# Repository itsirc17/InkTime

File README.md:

# InkTime

Designed for optimal energy efficiency, InkTime is a custom e-paper smartwatch project. This document serves as a complete technical reference for the project.

## Block Diagram(Architecture)

```mermaid
graph TD
    %% Central MCU
    MCU[nRF52840 Microcontroller]

    %% Power Subsystem
    USB[USB-C Port] -->|5V VBUS| ESD[ESD Protection USBLC6]
    ESD -->|5V| CHG[BQ25180 LiPo Charger]
    DCDC -->|3.3V System Power| MCU
    DCDC -->|3.3V| SENSORS
    BATT[LiPo Battery] <--> CHG
    BATT <--> FG[MAX17048 Fuel Gauge]
    BATT -->|V_BAT| DCDC[RT6160 Buck-Boost DC/DC]

    %% Interconnects
    MCU <-->|I2C Bus| IMU[BMA421 Accelerometer]
    MCU <-->|I2C Bus| HAP[DRV2605 Haptic Driver]
    MCU <-->|I2C Bus| CHG
    MCU <-->|I2C Bus| FG

    MCU -->|SPI & Control| EPD[E-Paper Display Connector]
    MCU -->|PWM/Trigger| HAP
    HAP -->|Analog| LRA[Haptic Motor]

    %% Inputs
    BTN1[SW_UP] -->|GPIO| MCU
    BTN2[SW_ENT] -->|GPIO| MCU
    BTN3[SW_DN] -->|GPIO| MCU

    %% SWD
    SWD[TC2030-IDC SWD Port] <-->|Programming/Debug| MCU
```

## Functionality

### Power Subsystem & Energy Management

Charging Input: Power is supplied via a 16-pin USB-C connector. The data lines are safeguarded against plug-in transients by a USBLC6-2SC6Y TVS diode array.

Battery Charging (BQ25180): A highly integrated linear charger tailored for small wearables. It features power-path management (allowing the device to run on USB power while charging) and interfaces with the MCU via I2C for dynamic charge current configuration and fault monitoring.

Fuel Gauge (MAX17048): Connected directly to the battery, this IC determines the State-Of-Charge (SOC) using voltage measurements and characterization algorithms. This eliminates the need for a power-wasting current sense resistor, reporting battery percentages cleanly over I2C.

Voltage Regulation (RT6160): Because LiPo voltages fluctuate between 4.2V and 3.0V, this Buck-Boost converter guarantees a stable 3.3V supply. It bucks down when the battery is full and boosts up as it depletes, maximizing the usable battery cycle.

Power Consumption Targets: The system aims for < 10 µA in Deep Sleep (MCU + Sensors suspended + Power ICs quiescent). Active processing consumes roughly 4-6 mA, while a display update will draw 10-15 mA for 2-3 seconds depending on the panel.

### Motion Sensing

IMU (BMA421): A Bosch ultra-low-power accelerometer optimized for wearables. It features a built-in hardware step-counter, allowing the MCU to remain in deep sleep while the sensor actively counts steps. The MCU only wakes periodically to sync the data via I2C.

### User Interface & Output

E-Paper Display (EPD): Interfaces through a standard 24-pin FPC connector. The onboard charge-pump circuit utilizes MBR0530 diodes, inductors, and DMG2305UX switching MOSFETs to generate the high drive voltages (+15V/-15V) needed to manipulate the e-ink microcapsules. The MCU can completely sever power to this circuit to prevent standby leakage.

Haptic Feedback (DRV2605): An I2C-connected haptic driver that contains an internal library of waveforms (clicks, buzzes, ramps). This delivers crisp tactile feedback to ERM or LRA motors without requiring the MCU to generate complex PWM signals.

Physical Inputs: Three tactile buttons (SW_UP, SW_ENT, SW_DN) feature hardware debouncing via 0.1uF capacitors. They utilize internal pull-ups and trigger MCU interrupts to wake the system from sleep.

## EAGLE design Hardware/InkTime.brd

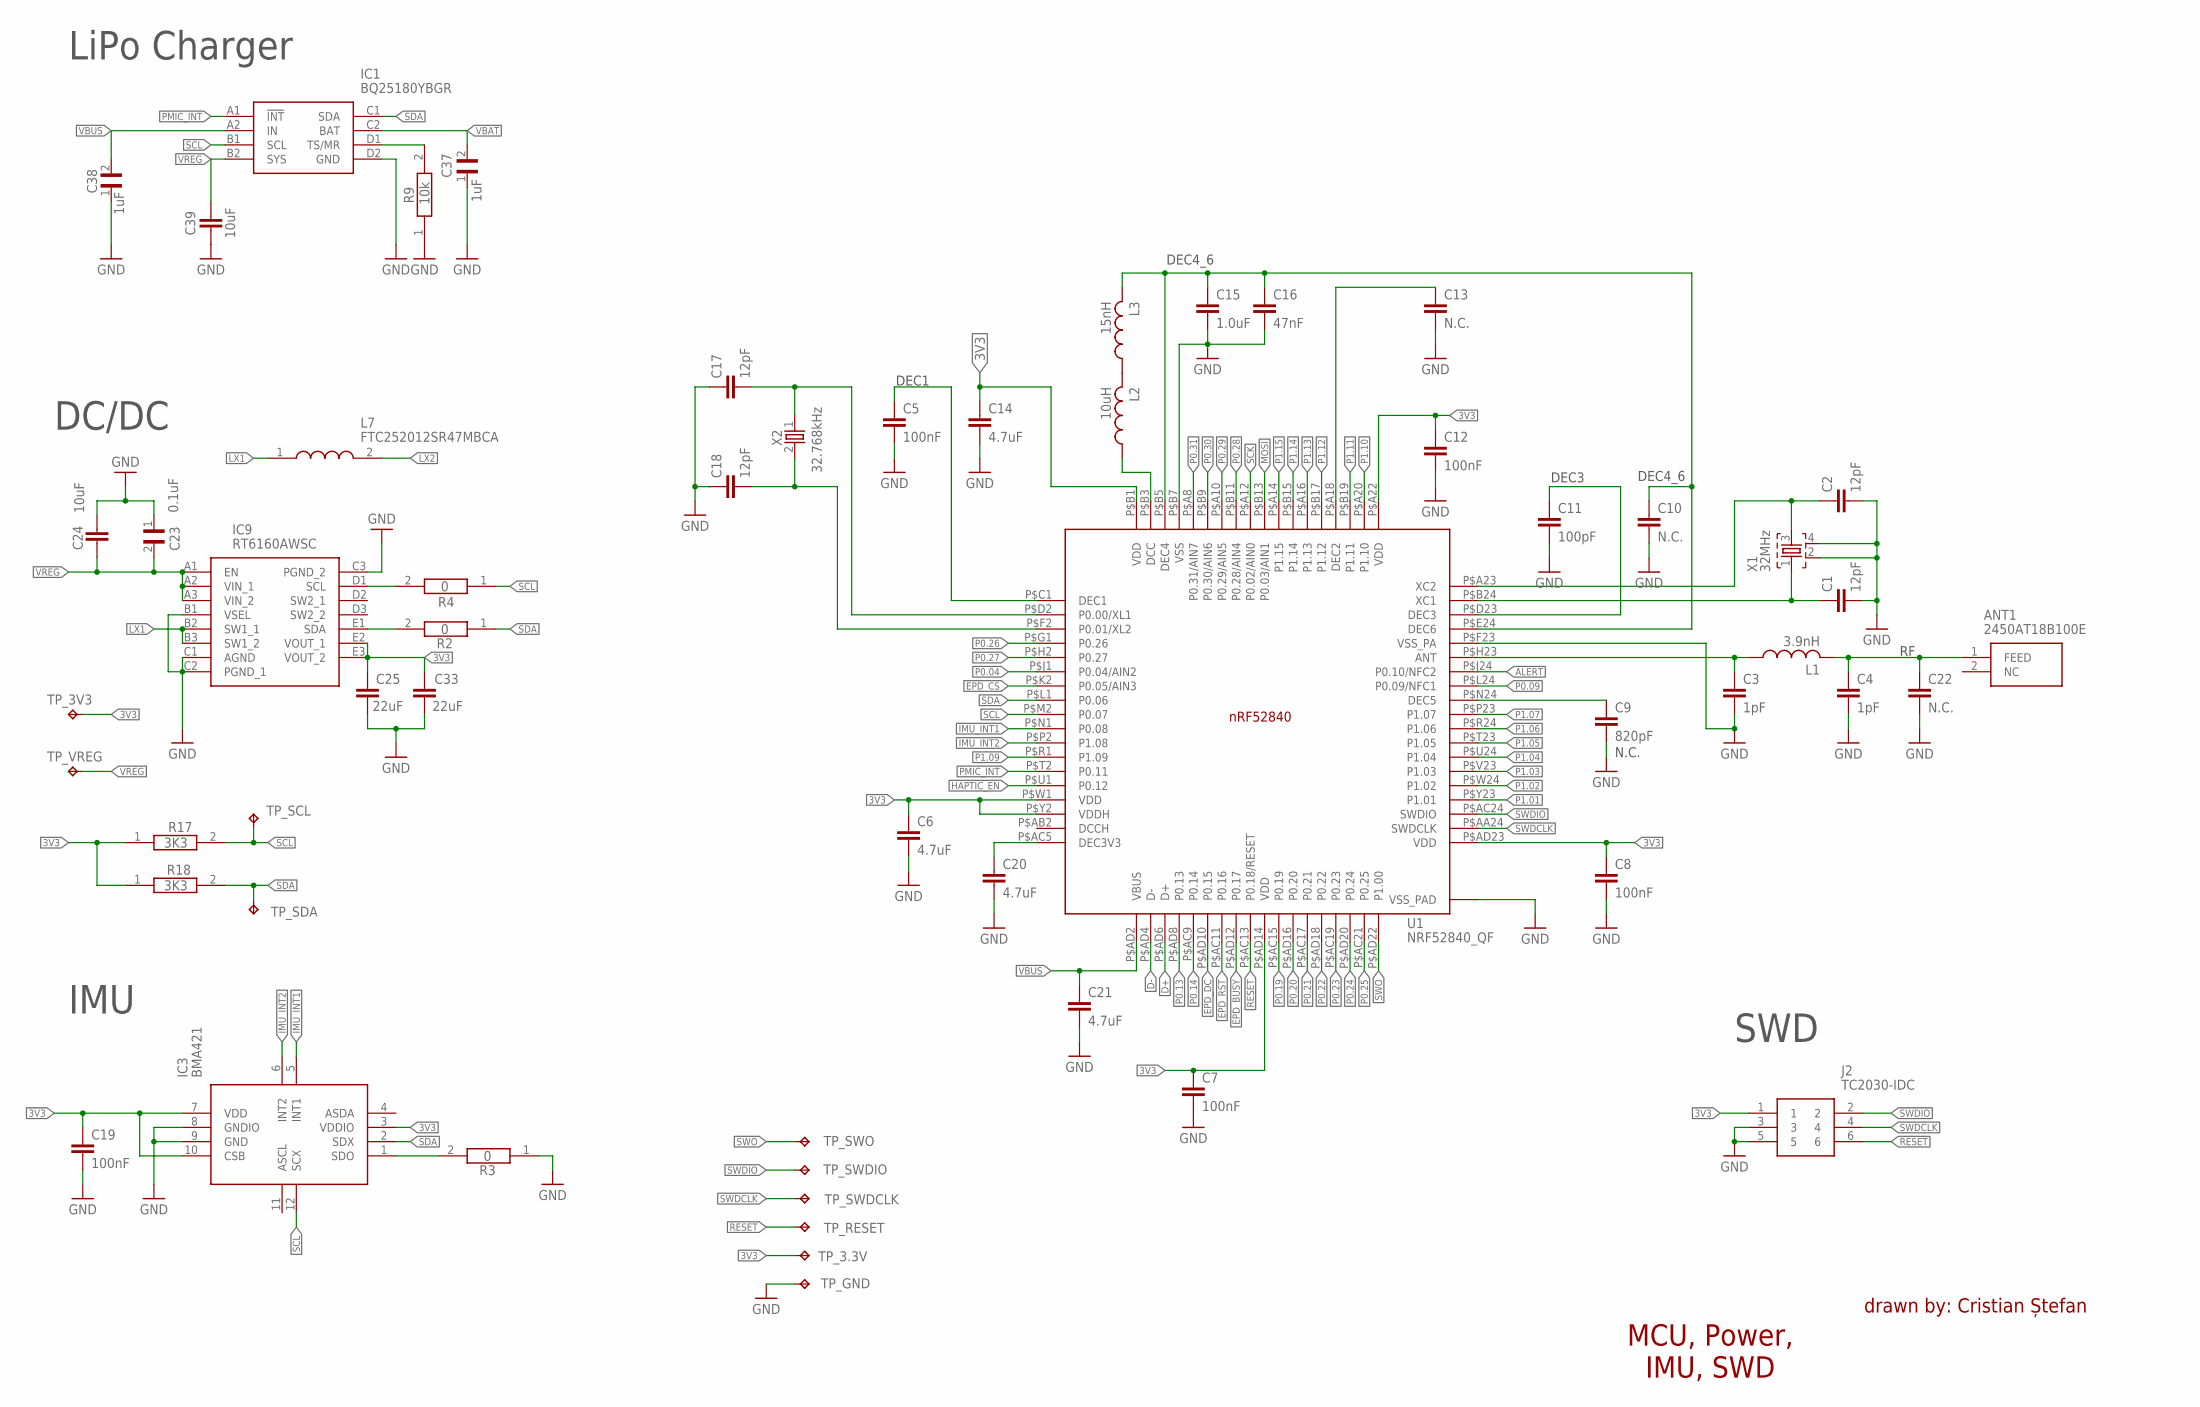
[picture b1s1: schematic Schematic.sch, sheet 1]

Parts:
ANT1: 2450AT18B100E; 2450AT18B100E_ANTC3216X140N
C1, C2, C17, C18: 12pF; NORDIC_NRF_3_RESC0201_L
C3, C4: 1pF; NORDIC_NRF_3_RESC0201_L
C5, C7, C8, C12, C19: 100nF; NORDIC_NRF_3_RESC0201_L
C6, C14, C20, C21: 4.7uF; NORDIC_NRF_3_RESC0402_L
C9: 820pF; NORDIC_NRF_3_RESC0201_L
C10, C13, C22: N.C.; NORDIC_NRF_3_RESC0201_L
C11: 100pF; NORDIC_NRF_3_RESC0201_L
C15: 1.0uF; NORDIC_NRF_3_RESC0402_L
C16: 47nF; NORDIC_NRF_3_RESC0201_L
C23: 0.1uF; GRM011R60J152KE01L_2_CAPC0201X13N
C24, C39: 10uF; NORDIC_NRF_3_RESC0402_L
C25, C33: 22uF; NORDIC_NRF_3_RESC0402_L
C37, C38: 1uF; GRM011R60J152KE01L_2_CAPC0201X13N
IC1: BQ25180YBGR; BQ25180YBGR_BGA8C40P2X4_100X155X50
IC3: BMA421; BMA423_BMA423
IC9: RT6160AWSC; RT6160AWSC_BGA15C40P3X5_140X230X60
J2: TC2030-IDC; TC2030-IDC_TC2030IDC
L1: 3.9nH; NORDIC_NRF_2_RESC0402_L
L2: 10uH; NORDIC_NRF_2_RESC0201_L
L3: 15nH; NORDIC_NRF_2_RESC0201_L
L7: FTC252012SR47MBCA; MLP2016SR47MT0S1_INDC2016X100N
R2, R3, R4: 0; CPF0201D7K68C1_0201
R9: 10k; CPF0201D7K68C1_0201
R17, R18: 3K3; CPF0201D7K68C1_0201
TP_3.3V, TP_3V3: HECTOR_WATCH_1_TPTP20R; HECTOR_WATCH_1_TP20R
TP_GND: HECTOR_WATCH_1_TPTP20R; HECTOR_WATCH_1_TP20R
TP_RESET: HECTOR_WATCH_1_TPTP20R; HECTOR_WATCH_1_TP20R
TP_SCL: HECTOR_WATCH_1_TPTP20R; HECTOR_WATCH_1_TP20R
TP_SDA: HECTOR_WATCH_1_TPTP20R; HECTOR_WATCH_1_TP20R
TP_SWDCLK: HECTOR_WATCH_1_TPTP20R; HECTOR_WATCH_1_TP20R
TP_SWDIO: HECTOR_WATCH_1_TPTP20R; HECTOR_WATCH_1_TP20R
TP_SWO: HECTOR_WATCH_1_TPTP20R; HECTOR_WATCH_1_TP20R
TP_VREG: HECTOR_WATCH_1_TPTP20R; HECTOR_WATCH_1_TP20R
U1: NRF52840_QF; NORDIC_NRF_4_AQFN50P700X700X85_HS-74N
X1: 32MHz; NORDIC_NRF_BT-XTAL_2016_N
X2: 32.768kHz; NORDIC_NRF_1_XTAL_3215_N

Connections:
3V3: C6.1, C7.1, C8.1, C12.1, C14.1, C19.1, C25.2, C33.2, IC3.3 (VDDIO), IC3.7 (VDD), IC3.10 (CSB), IC9.E2 (VOUT_1), IC9.E3 (VOUT_2), J2.1, R17.1, R18.1, TP_3.3V.TP, TP_3V3.TP, U1.P$A22 (VDD), U1.P$AD14 (VDD), U1.P$AD23 (VDD), U1.P$B1 (VDD), U1.P$W1 (VDD), U1.P$Y2 (VDDH); also elsewhere on the board
ALERT: U1.P$J24 (P0.10/NFC2); also elsewhere on the board
CACA: C5.1, U1.P$C1 (DEC1)
CACA2: C13.1, U1.P$A18 (DEC2)
D+: U1.P$AD6 (D+); also elsewhere on the board
D-: U1.P$AD4 (D-); also elsewhere on the board
EPD_BUSY: U1.P$AD12 (P0.17); also elsewhere on the board
EPD_CS: U1.P$K2 (P0.05/AIN3); also elsewhere on the board
EPD_DC: U1.P$AD10 (P0.15); also elsewhere on the board
EPD_RST: U1.P$AC11 (P0.16); also elsewhere on the board
GND: C1.2, C2.2, C3.2, C4.2, C5.2, C6.2, C7.2, C8.2, C9.2, C10.2, C11.2, C12.2, C13.2, C14.2, C15.2, C16.2, C17.1, C18.1, C19.2, C20.2, C21.2, C22.2, C23.1, C24.1, C25.1, C33.1, C37.1, C38.1, C39.2, IC1.D2 (GND), IC3.8 (GNDIO), IC3.9 (GND), IC9.B1 (VSEL), IC9.C1 (AGND), IC9.C2 (PGND_1), IC9.C3 (PGND_2), J2.3, J2.5, R3.1, R9.1, TP_GND.TP, U1.P$74 (VSS_PAD), U1.P$75 (VSS_PAD), U1.P$76 (VSS_PAD), U1.P$77 (VSS_PAD), U1.P$78 (VSS_PAD), U1.P$79 (VSS_PAD), U1.P$80 (VSS_PAD), U1.P$81 (VSS_PAD), U1.P$82 (VSS_PAD), U1.P$83 (VSS_PAD), U1.P$84 (VSS_PAD), U1.P$85 (VSS_PAD), U1.P$86 (VSS_PAD), U1.P$87 (VSS_PAD), U1.P$88 (VSS_PAD), U1.P$89 (VSS_PAD), U1.P$90 (VSS_PAD), U1.P$B7 (VSS), U1.P$F23 (VSS_PA), X1.2, X1.4; also elsewhere on the board
HAPTIC_EN: U1.P$U1 (P0.12); also elsewhere on the board
IMU_INT1: IC3.5 (INT1), U1.P$N1 (P0.08)
IMU_INT2: IC3.6 (INT2), U1.P$P2 (P1.08)
LX1: IC9.B2 (SW1_1), IC9.B3 (SW1_2), L7.1
LX2: L7.2
MOSI: U1.P$B13 (P0.03/AIN1); also elsewhere on the board
unnamed: IC9.E1 (SDA), R2.2
unnamed: IC9.D1 (SCL), R4.2
unnamed: IC3.1 (SDO), R3.2
unnamed: C20.1, U1.P$AC5 (DEC3V3)
unnamed: C9.1, U1.P$N24 (DEC5)
unnamed: C3.1, L1.1, U1.P$H23 (ANT)
unnamed: C2.1, U1.P$A23 (XC2), X1.3
unnamed: ANT1.1 (FEED), C4.1, C22.1, L1.2
unnamed: C11.1, U1.P$D23 (DEC3)
unnamed: IC1.D1 (TS/MR), R9.2
unnamed: L2.2, L3.1
unnamed: C1.1, U1.P$B24 (XC1), X1.1
unnamed: C17.2, U1.P$D2 (P0.00/XL1), X2.1
unnamed: L2.1, U1.P$B3 (DCC)
unnamed: C10.1, C15.1, C16.1, L3.2, U1.P$B5 (DEC4), U1.P$E24 (DEC6)
unnamed: C18.2, U1.P$F2 (P0.01/XL2), X2.2
P0.04: U1.P$J1 (P0.04/AIN2)
P0.09: U1.P$L24 (P0.09/NFC1)
P0.13: U1.P$AD8 (P0.13); also elsewhere on the board
P0.14: U1.P$AC9 (P0.14); also elsewhere on the board
P0.19: U1.P$AC15 (P0.19)
P0.20: U1.P$AD16 (P0.20)
P0.21: U1.P$AC17 (P0.21)
P0.22: U1.P$AD18 (P0.22)
P0.23: U1.P$AC19 (P0.23)
P0.24: U1.P$AD20 (P0.24)
P0.25: U1.P$AC21 (P0.25)
P0.26: U1.P$G1 (P0.26)
P0.27: U1.P$H2 (P0.27)
P0.28: U1.P$B11 (P0.28/AIN4)
P0.29: U1.P$A10 (P0.29/AIN5)
P0.30: U1.P$B9 (P0.30/AIN6)
P0.31: U1.P$A8 (P0.31/AIN7)
P1.01: U1.P$Y23 (P1.01); also elsewhere on the board
P1.02: U1.P$W24 (P1.02); also elsewhere on the board
P1.03: U1.P$V23 (P1.03)
P1.04: U1.P$U24 (P1.04)
P1.05: U1.P$T23 (P1.05)
P1.06: U1.P$R24 (P1.06)
P1.07: U1.P$P23 (P1.07)
P1.09: U1.P$R1 (P1.09)
P1.10: U1.P$A20 (P1.10)
P1.11: U1.P$B19 (P1.11)
P1.12: U1.P$B17 (P1.12)
P1.13: U1.P$A16 (P1.13)
P1.14: U1.P$B15 (P1.14)
P1.15: U1.P$A14 (P1.15)
PMIC_INT: IC1.A1 (!INT), U1.P$T2 (P0.11)
RESET: J2.6, TP_RESET.TP, U1.P$AC13 (P0.18/RESET)
SCK: U1.P$A12 (P0.02/AIN0); also elsewhere on the board
SCL: IC1.B1 (SCL), IC3.12 (SCX), R4.1, R17.2, TP_SCL.TP, U1.P$M2 (P0.07); also elsewhere on the board
SDA: IC1.C1 (SDA), IC3.2 (SDX), R2.1, R18.2, TP_SDA.TP, U1.P$L1 (P0.06); also elsewhere on the board
SWDCLK: J2.4, TP_SWDCLK.TP, U1.P$AA24 (SWDCLK)
SWDIO: J2.2, TP_SWDIO.TP, U1.P$AC24 (SWDIO)
SWO: TP_SWO.TP, U1.P$AD22 (P1.00)
VBAT: C37.2, IC1.C2 (BAT); also elsewhere on the board
VBUS: C21.1, C38.2, IC1.A2 (IN), U1.P$AD2 (VBUS); also elsewhere on the board
VREG: C23.2, C24.2, C39.1, IC1.B2 (SYS), IC9.A1 (EN), IC9.A2 (VIN_1), IC9.A3 (VIN_2), TP_VREG.TP

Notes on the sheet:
LiPo Charger
N.C.
DEC4_6
DEC3
DEC1
DC/DC
IMU
SWD
drawn by: Cristian Ștefan
MCU, Power, IMU, SWD

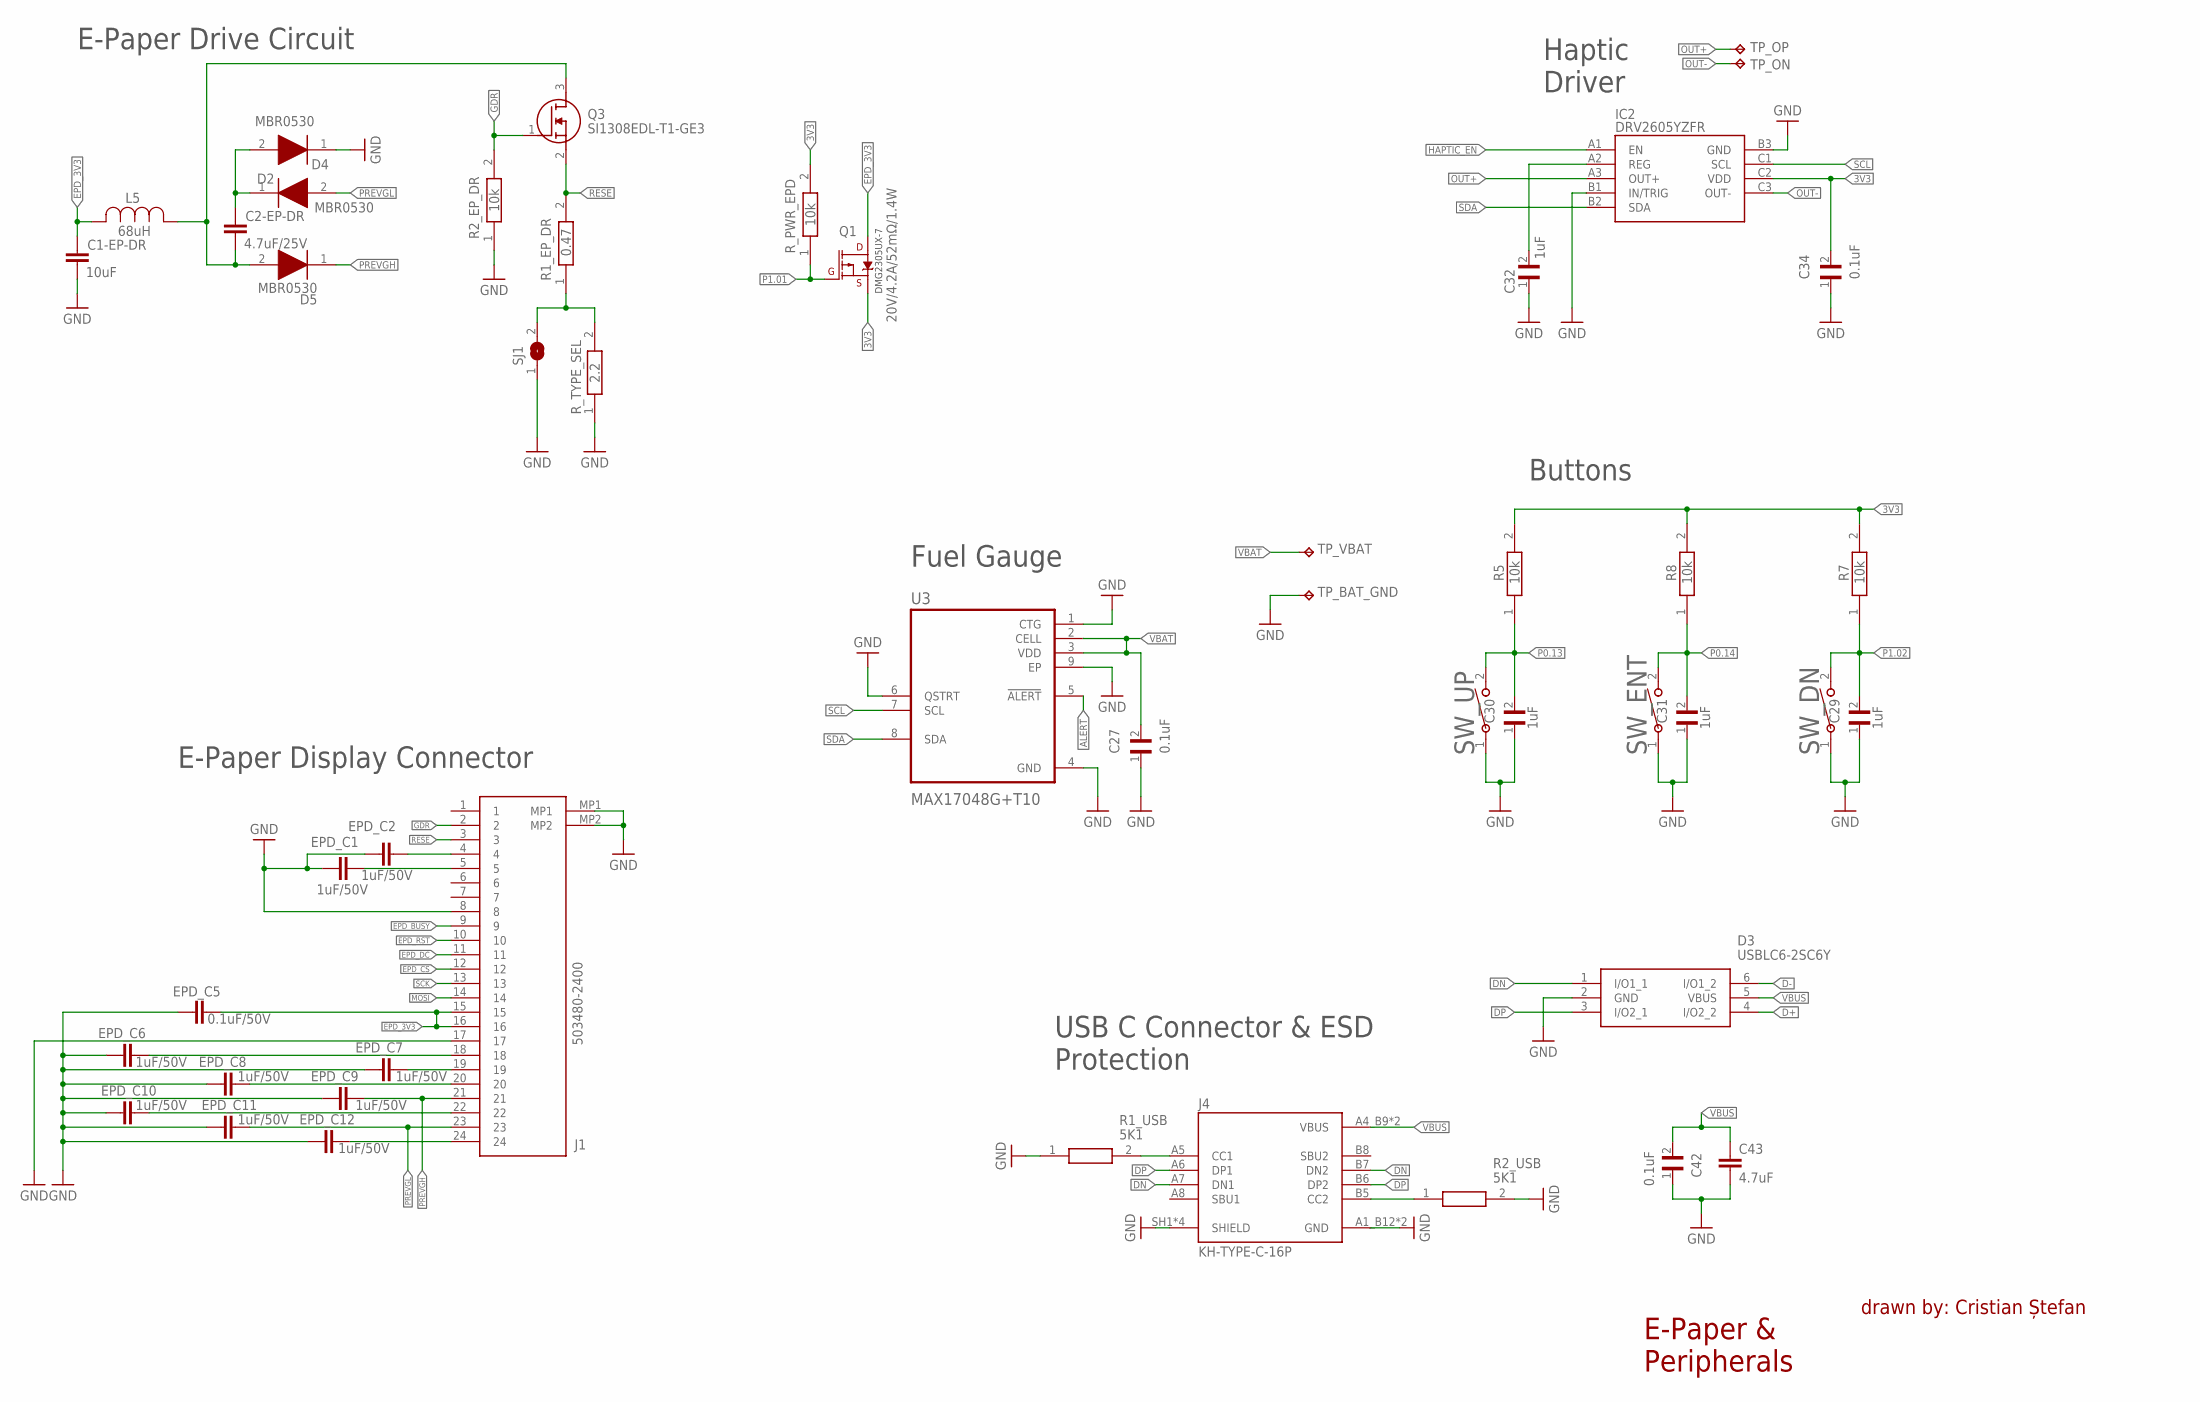
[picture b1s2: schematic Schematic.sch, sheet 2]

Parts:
C1-EP-DR: 10uF; NORDIC_NRF_3_RESC0402_L
C2-EP-DR: 4.7uF/25V; NORDIC_NRF_3_RESC0402_L
C27, C34, C42: 0.1uF; GRM011R60J152KE01L_2_CAPC0201X13N
C29, C30, C31, C32: 1uF; GRM011R60J152KE01L_2_CAPC0201X13N
C43: 4.7uF; NORDIC_NRF_3_RESC0402_L
D2, D4, D5: MBR0530; ESP32_C6_LIBRARY_5_SOD3716X135N
D3: USBLC6-2SC6Y; ESP32_C6_LIBRARY_3_SOT95P280X145-6N
EPD_C1, EPD_C2, EPD_C6, EPD_C7, EPD_C8, EPD_C9, EPD_C10, EPD_C11, EPD_C12: 1uF/50V; NORDIC_NRF_3_RESC0402_L
EPD_C5: 0.1uF/50V; NORDIC_NRF_3_RESC0402_L
IC2: DRV2605YZFR; DRV2605YZFR_BGA9C50P3X3_144X144X62
J1: 503480-2400; 503480-2400_5034802400
J4: KH-TYPE-C-16P; KH-TYPE-C-16P_KINGHELM_KH-TYPE-C-16P
L5: 68uH; ESP32_C6_LIBRARY_2_IND_4828-WE-TPC_WRE
Q1: 20V/4.2A/52mΩ/1.4W; ESP32_C6_LIBRARY_4_ESP32_C6_LIBRARY_4_ESP32_C6_LIBRARY_4_ES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
Q3: SI1308EDL-T1-GE3; ESP32_C6_LIBRARY_6_SOT65P210X110-3N
R1_EP_DR: 0.47; CPF0201D7K68C1_0201
R1_USB, R2_USB: 5K1; CPF0201D7K68C1_0201
R2_EP_DR, R5, R7, R8: 10k; CPF0201D7K68C1_0201
R_PWR_EPD: 10k; CPF0201D7K68C1_0201
R_TYPE_SEL: 2.2; CPF0201D7K68C1_0201
SJ1: ESP32_C6_LIBRARY_7_JUMPER_SJ
SW_DN: 2025-10-22_07-23-44_LIBRARY_EVP-AKE31A; 2025-10-22_07-23-44_LIBRARY_SW_EVP-AKE31A_PAN
SW_ENT: 2025-10-22_07-23-44_LIBRARY_EVP-AKE31A; 2025-10-22_07-23-44_LIBRARY_SW_EVP-AKE31A_PAN
SW_UP: 2025-10-22_07-23-44_LIBRARY_EVP-AKE31A; 2025-10-22_07-23-44_LIBRARY_SW_EVP-AKE31A_PAN
TP_BAT_GND: HECTOR_WATCH_1_TPTP20R; HECTOR_WATCH_1_TP20R
TP_ON: HECTOR_WATCH_1_TPTP20R; HECTOR_WATCH_1_TP20R
TP_OP: HECTOR_WATCH_1_TPTP20R; HECTOR_WATCH_1_TP20R
TP_VBAT: HECTOR_WATCH_1_TPTP20R; HECTOR_WATCH_1_TP20R
U3: MAX17048G+T10; ESP32_C6_LIBRARY_SON50P200X200X80-9N

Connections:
3V3: C34.2, IC2.C2 (VDD), Q1.2 (S), R5.2, R7.2, R8.2, R_PWR_EPD.2; also elsewhere on the board
ALERT: U3.5 (!ALERT); also elsewhere on the board
D+: D3.4 (I/O2_2); also elsewhere on the board
D-: D3.6 (I/O1_2); also elsewhere on the board
DN: D3.1 (I/O1_1), J4.A7 (DN1), J4.B7 (DN2)
DP: D3.3 (I/O2_1), J4.A6 (DP1), J4.B6 (DP2)
EPD_3V3: C1-EP-DR.1, EPD_C5.2, J1.15, J1.16, L5.2, Q1.3 (D)
EPD_BUSY: J1.9; also elsewhere on the board
EPD_CS: J1.12; also elsewhere on the board
EPD_DC: J1.11; also elsewhere on the board
EPD_RST: J1.10; also elsewhere on the board
GDR: J1.2, Q3.1 (G), R2_EP_DR.2
GND: C1-EP-DR.2, C27.1, C29.1, C30.1, C31.1, C32.1, C34.1, C42.1, C43.2, D3.2 (GND), D4.1 (K), EPD_C1.1, EPD_C2.1, EPD_C5.1, EPD_C6.1, EPD_C7.1, EPD_C8.1, EPD_C9.1, EPD_C10.1, EPD_C11.1, EPD_C12.1, IC2.B1 (IN/TRIG), IC2.B3 (GND), J1.8, J1.17, J1.MP1, J1.MP2, J4.A1_B12 (GND), J4.A12_B1 (GND), J4.SH1 (SHIELD), J4.SH2 (SHIELD), J4.SH3 (SHIELD), J4.SH4 (SHIELD), R1_USB.1, R2_EP_DR.1, R2_USB.2, R_TYPE_SEL.1, SJ1.1, SW_DN.1, SW_ENT.1, SW_UP.1, TP_BAT_GND.TP, U3.1 (CTG), U3.4 (GND), U3.6 (QSTRT), U3.9 (EP); also elsewhere on the board
HAPTIC_EN: IC2.A1 (EN); also elsewhere on the board
MOSI: J1.14; also elsewhere on the board
unnamed: C2-EP-DR.1, D2.1 (K), D4.2 (A)
unnamed: J4.B5 (CC2), R2_USB.1
unnamed: R1_EP_DR.1, R_TYPE_SEL.2, SJ1.2
unnamed: C2-EP-DR.2, D5.2 (A), L5.1, Q3.3 (D)
unnamed: EPD_C2.2, J1.4
unnamed: C32.2, IC2.A2 (REG)
unnamed: EPD_C1.2, J1.5
unnamed: EPD_C6.2, J1.18
unnamed: EPD_C7.2, J1.19
unnamed: J4.A5 (CC1), R1_USB.2
unnamed: EPD_C8.2, J1.20
unnamed: EPD_C10.2, J1.22
unnamed: EPD_C12.2, J1.24
OUT+: IC2.A3 (OUT+), TP_OP.TP
OUT-: IC2.C3 (OUT-), TP_ON.TP
P0.13: C30.2, R5.1, SW_UP.2; also elsewhere on the board
P0.14: C31.2, R8.1, SW_ENT.2; also elsewhere on the board
P1.01: Q1.1 (G), R_PWR_EPD.1; also elsewhere on the board
P1.02: C29.2, R7.1, SW_DN.2; also elsewhere on the board
PREVGH: D5.1 (K), EPD_C9.2, J1.21
PREVGL: D2.2 (A), EPD_C11.2, J1.23
RESE: J1.3, Q3.2 (S), R1_EP_DR.2
SCK: J1.13; also elsewhere on the board
SCL: IC2.C1 (SCL), U3.7 (SCL); also elsewhere on the board
SDA: IC2.B2 (SDA), U3.8 (SDA); also elsewhere on the board
VBAT: C27.2, TP_VBAT.TP, U3.2 (CELL), U3.3 (VDD); also elsewhere on the board
VBUS: C42.2, C43.1, D3.5 (VBUS), J4.A4_B9 (VBUS), J4.A9_B4 (VBUS); also elsewhere on the board

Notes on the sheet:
DMG2305UX-7
E-Paper Drive Circuit
Haptic Driver
Buttons
Fuel Gauge
USB C Connector & ESD Protection
E-Paper Display Connector
drawn by: Cristian Ștefan
E-Paper & Peripherals

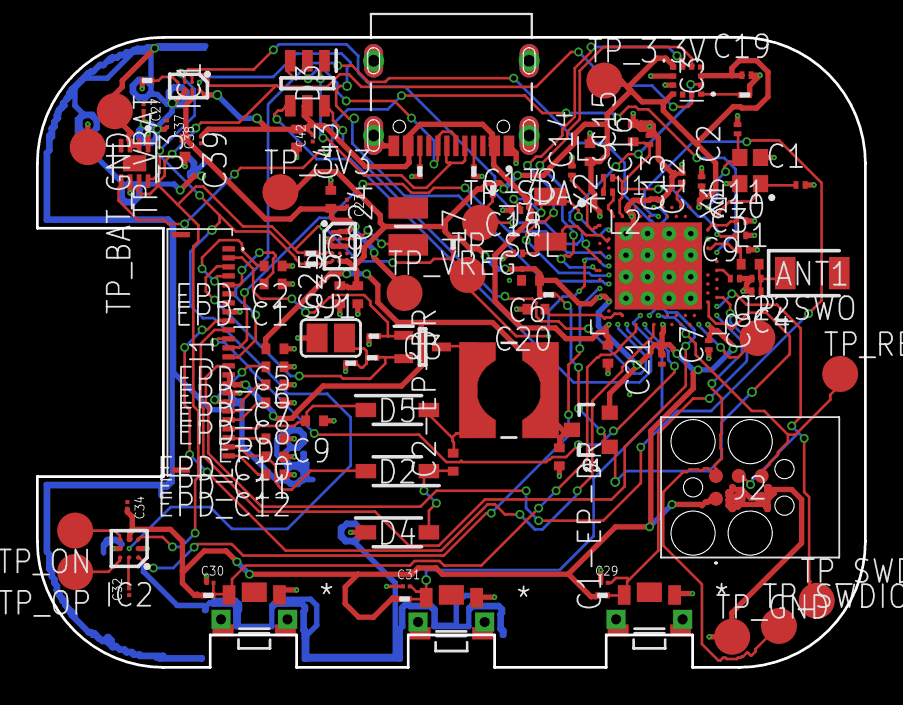
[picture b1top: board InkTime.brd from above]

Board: 4 copper layers, 46.0 x 35.0 mm, 105 parts (0 on the bottom side), 69 nets.

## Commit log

2026-04-10 added Hardware Folder
2026-04-10 added Schematic.sch
2026-04-10 added project name 'InkTime' to README
2026-04-20 Updated Hardware
2026-04-20 Added Manufacturing
2026-04-20 Added Images
2026-04-20 Added Mechanical
2026-04-20 Added LICENSE
2026-04-20 Added Block Diagram

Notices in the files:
parts and their libraries:
COPYRIGHT: Copyright (C) 2024 Ultra Librarian. All rights reserved.
